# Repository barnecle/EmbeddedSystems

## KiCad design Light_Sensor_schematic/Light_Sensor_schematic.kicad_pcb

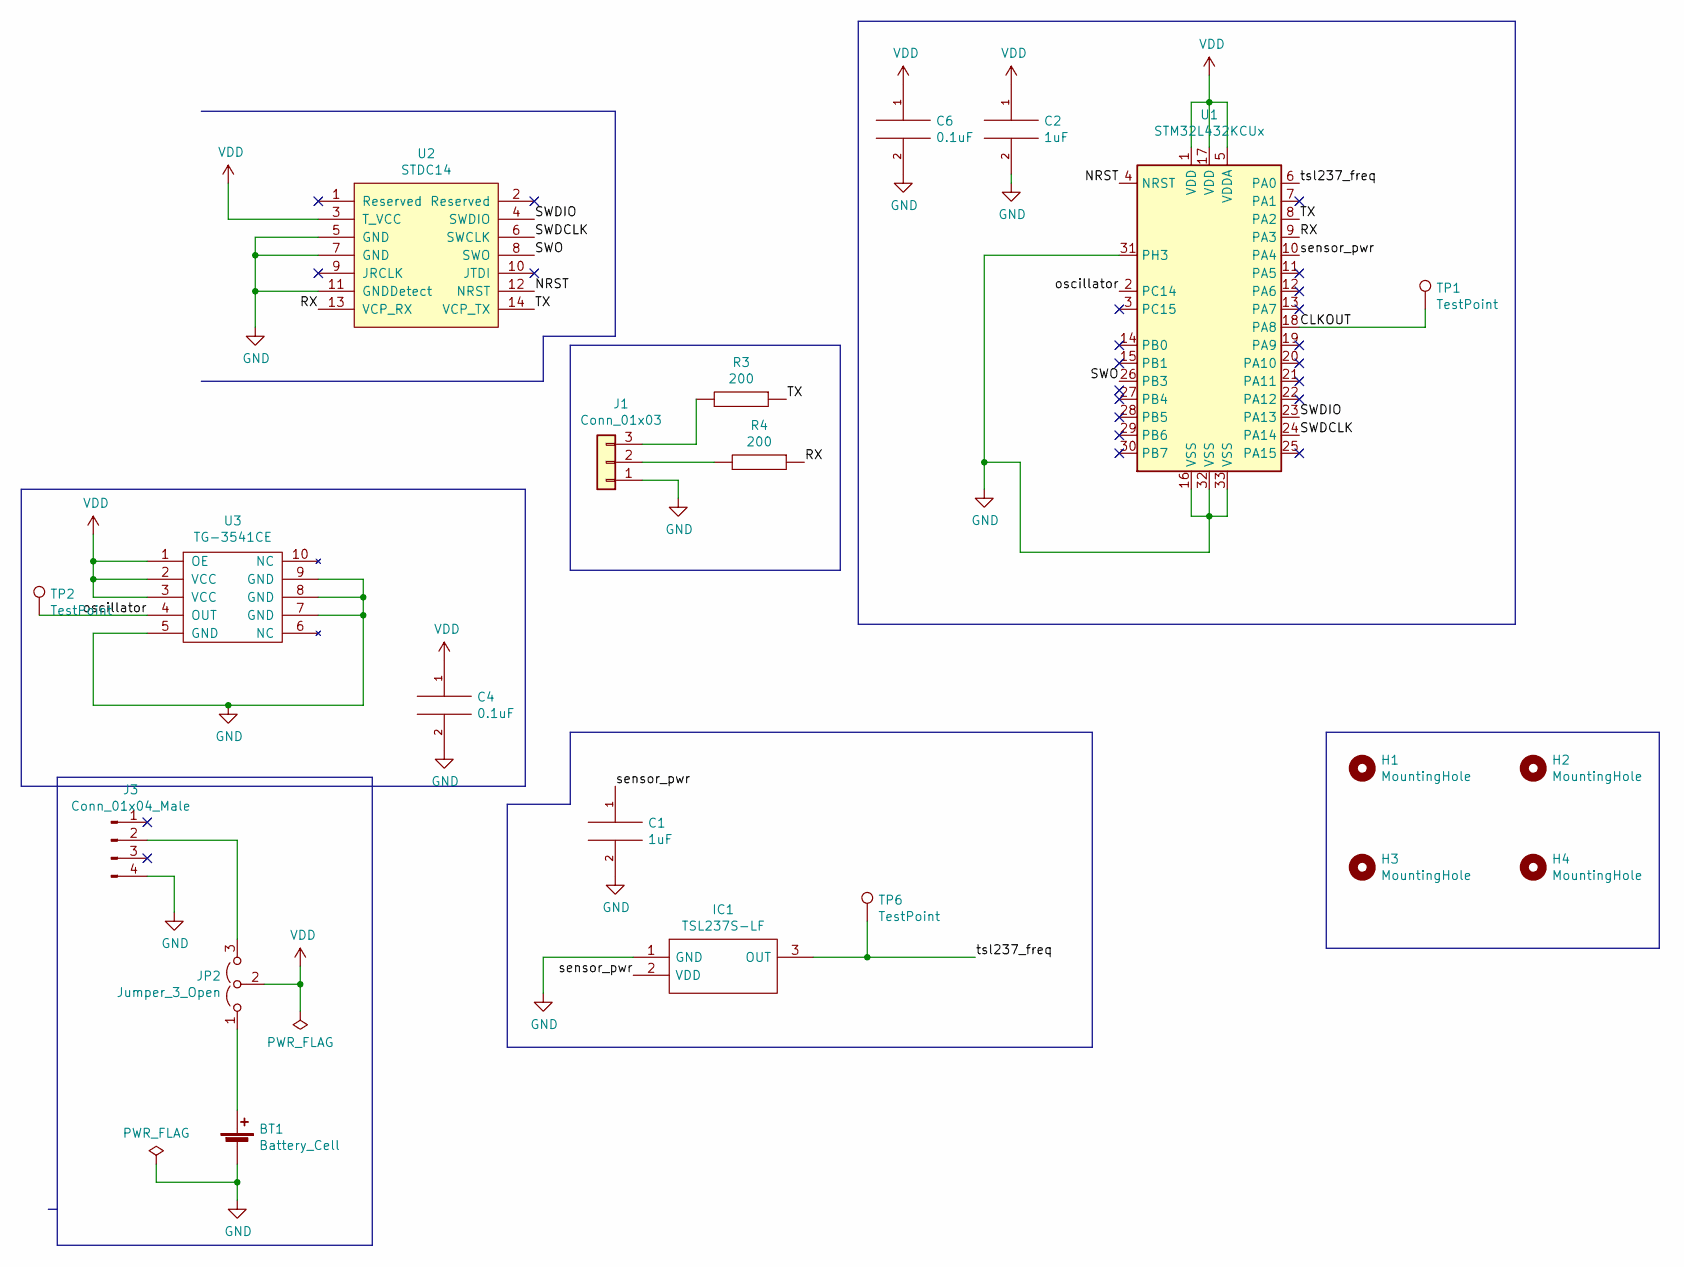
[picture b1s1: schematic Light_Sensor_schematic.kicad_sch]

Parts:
BT1: Battery_Cell; BatteryHolder_Keystone_1060_1x2032
C1, C2: 1uF; C_0603_1608Metric_Pad1.08x0.95mm_HandSolder
C4, C6: 0.1uF; C_0603_1608Metric_Pad1.08x0.95mm_HandSolder
H1, H2, H3, H4: MountingHole; MountingHole_2.2mm_M2_Pad_Via
IC1: TSL237S-LF; Mouser Part Number 856-TSL237S-LF
J1: Conn_01x03; JST_XH_B3B-XH-AM_1x03_P2.50mm_Vertical
J3: Conn_01x04_Male; JST_XH_B4B-XH-AM_1x04_P2.50mm_Vertical
JP2: Jumper_3_Open; SolderJumper-3_P1.3mm_Open_RoundedPad1.0x1.5mm
R3, R4: 200; R_0603_1608Metric_Pad0.98x0.95mm_HandSolder
TP1, TP2, TP6: TestPoint; TestPoint_Pad_D1.5mm
U1: STM32L432KCUx; QFN-32-1EP_5x5mm_P0.5mm_EP3.45x3.45mm
U2: STDC14; ftsh_14p_connector
U3: TG-3541CE

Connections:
/CLKOUT: TP1.1, U1.18 (PA8)
/NRST: U1.4 (NRST), U2.12 (NRST)
/RX: R4.1, U1.9 (PA3), U2.13 (VCP_RX)
/SWDCLK: U1.24 (PA14), U2.6 (SWCLK)
/SWDIO: U1.23 (PA13), U2.4 (SWDIO)
/SWO: U1.26 (PB3), U2.8 (SWO)
/TX: R3.1, U1.8 (PA2), U2.14 (VCP_TX)
/oscillator: TP2.1, U1.2 (PC14), U3.4 (OUT)
/sensor_pwr: C1.1, IC1.2 (VDD), U1.10 (PA4)
/tsl237_freq: IC1.3 (OUT), TP6.1, U1.6 (PA0)
GND: BT1.2 (-), C1.2, C2.2, C4.2, C6.2, IC1.1 (GND), J1.1, J3.4, U1.16 (VSS), U1.31 (PH3), U1.32 (VSS), U1.33 (VSS), U2.5 (GND), U2.7 (GND), U2.11 (GNDDetect), U3.5 (GND), U3.7 (GND), U3.8 (GND), U3.9 (GND)
unnamed: BT1.1 (+), JP2.1 (A)
unnamed: J1.2, R4.2
unnamed: J1.3, R3.2
unnamed: J3.2, JP2.3 (B)
VDD: C2.1, C4.1, C6.1, JP2.2 (C), U1.1 (VDD), U1.5 (VDDA), U1.17 (VDD), U2.3 (T_VCC), U3.1 (OE), U3.2 (VCC), U3.3 (VCC)

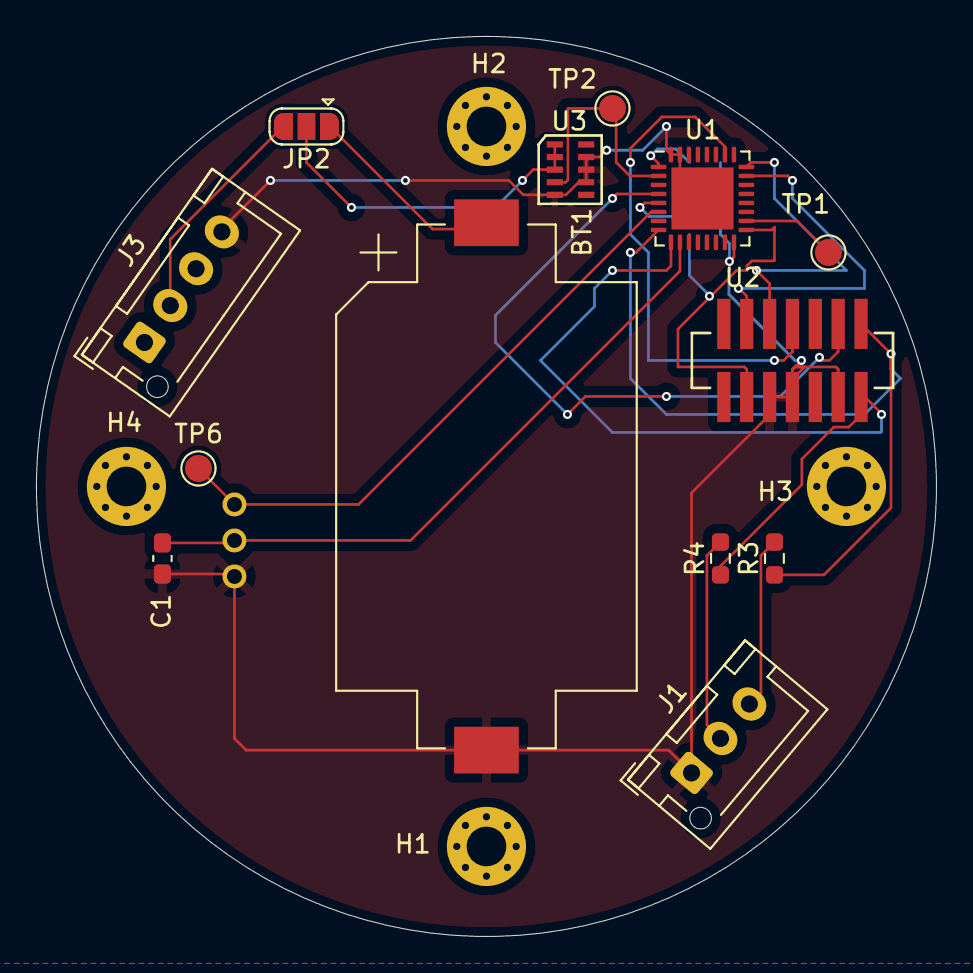
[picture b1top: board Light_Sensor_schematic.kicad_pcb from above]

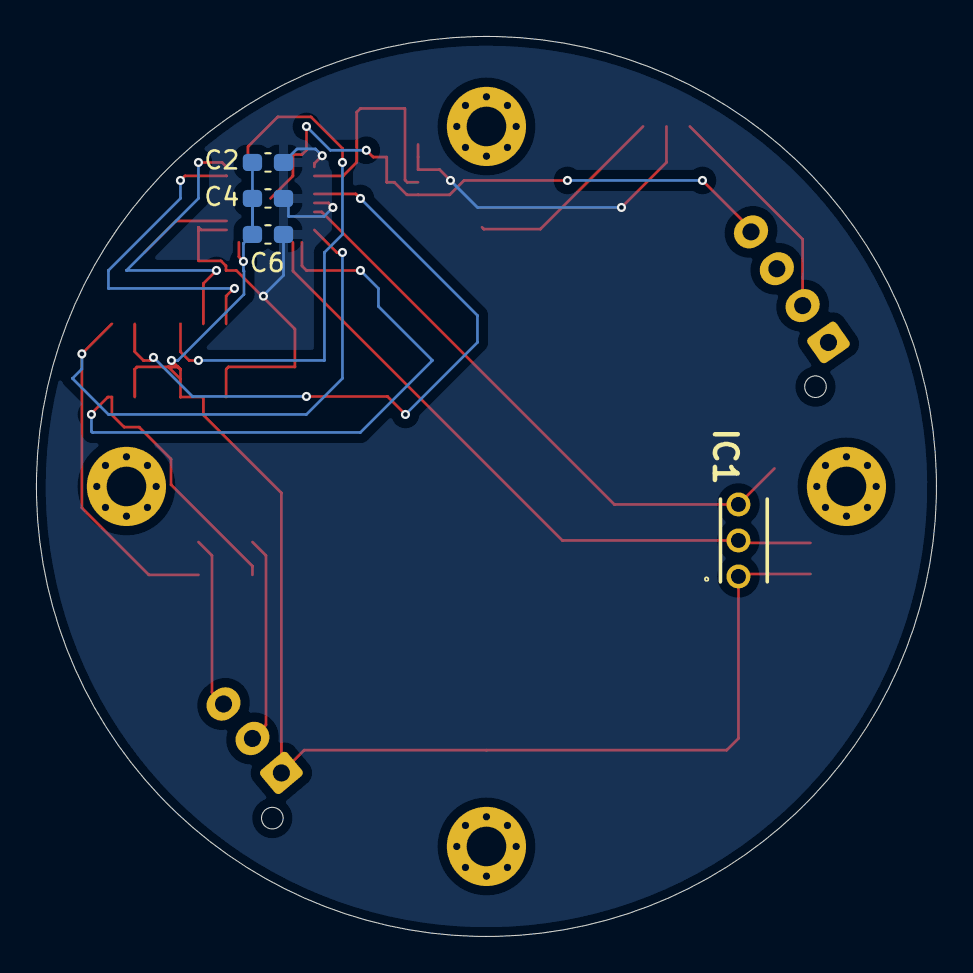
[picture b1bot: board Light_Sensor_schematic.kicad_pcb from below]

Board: 2 copper layers, 50.0 x 50.0 mm, 21 parts (4 on the bottom side), 16 nets.

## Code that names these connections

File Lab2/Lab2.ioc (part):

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Mcu.Name=STM32L412KBUx
Mcu.Package=UFQFPN32
Mcu.UserName=STM32L412KBUx
PA0-CK_IN.Mode=HSE-External-Clock-Source-for-LittleOrca
PA0-CK_IN.Signal=RCC_CK_IN
PA13\ (JTMS/SWDIO).GPIOParameters=GPIO_Label
PA13\ (JTMS/SWDIO).GPIO_Label=SWDIO
PA13\ (JTMS/SWDIO).Mode=Serial_Wire
PA13\ (JTMS/SWDIO).Signal=SYS_JTMS-SWDIO
PA14\ (JTCK/SWCLK).GPIOParameters=GPIO_Label
PA14\ (JTCK/SWCLK).GPIO_Label=SWCLK
PA14\ (JTCK/SWCLK).Mode=Serial_Wire
PA14\ (JTCK/SWCLK).Signal=SYS_JTCK-SWCLK
PA15\ (JTDI).GPIOParameters=GPIO_Label
PA15\ (JTDI).GPIO_Label=VCP_RX
PA15\ (JTDI).Mode=Asynchronous
PA15\ (JTDI).Signal=USART2_RX
PA2.GPIOParameters=GPIO_Label
PA2.GPIO_Label=VCP_TX
PA2.Mode=Asynchronous
PA2.Signal=USART2_TX
PB3\ (JTDO/TRACESWO).GPIOParameters=GPIO_Label
PB3\ (JTDO/TRACESWO).GPIO_Label=LD3 [Green]
PB3\ (JTDO/TRACESWO).Signal=GPIO_Output
PC14-OSC32_IN\ (PC14).Mode=LSE-External-Oscillator
PC14-OSC32_IN\ (PC14).Signal=RCC_OSC32_IN
PC15-OSC32_OUT\ (PC15).Mode=LSE-External-Oscillator
PC15-OSC32_OUT\ (PC15).Signal=RCC_OSC32_OUT
RCC.HSE_VALUE=8000000
RCC.SYSCLKFreq_VALUE=32000000
board=NUCLEO-L412KB
boardIOC=true

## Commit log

2022-01-22 lab 1
2022-02-02 lab 2 done
2022-02-04 alternate lab2
2022-02-06 command line implementation
2022-02-11 lab3 done
2022-02-18 lab 4 started
2022-02-21 lab4 done
2022-02-26 lab5 initial
2022-02-26 lab5 done
2022-03-04 lab6 done
2022-03-26 Lab 7
2022-03-26 Lab 7 schematic
2022-03-29 last components added to BOM
2022-04-02 Lab 8
2022-04-12 lab9 done
2022-04-12 Lab 7 writeup
2022-04-19 lid for price est
2022-04-19 lab10 half done
2022-04-20 Kicad5 to 6
2022-04-20 add hat part
2022-04-20 corrected DRC errors to allow import at macrofab.
2022-04-21 Mfg analysis
2022-04-25 lab7 pdfs
